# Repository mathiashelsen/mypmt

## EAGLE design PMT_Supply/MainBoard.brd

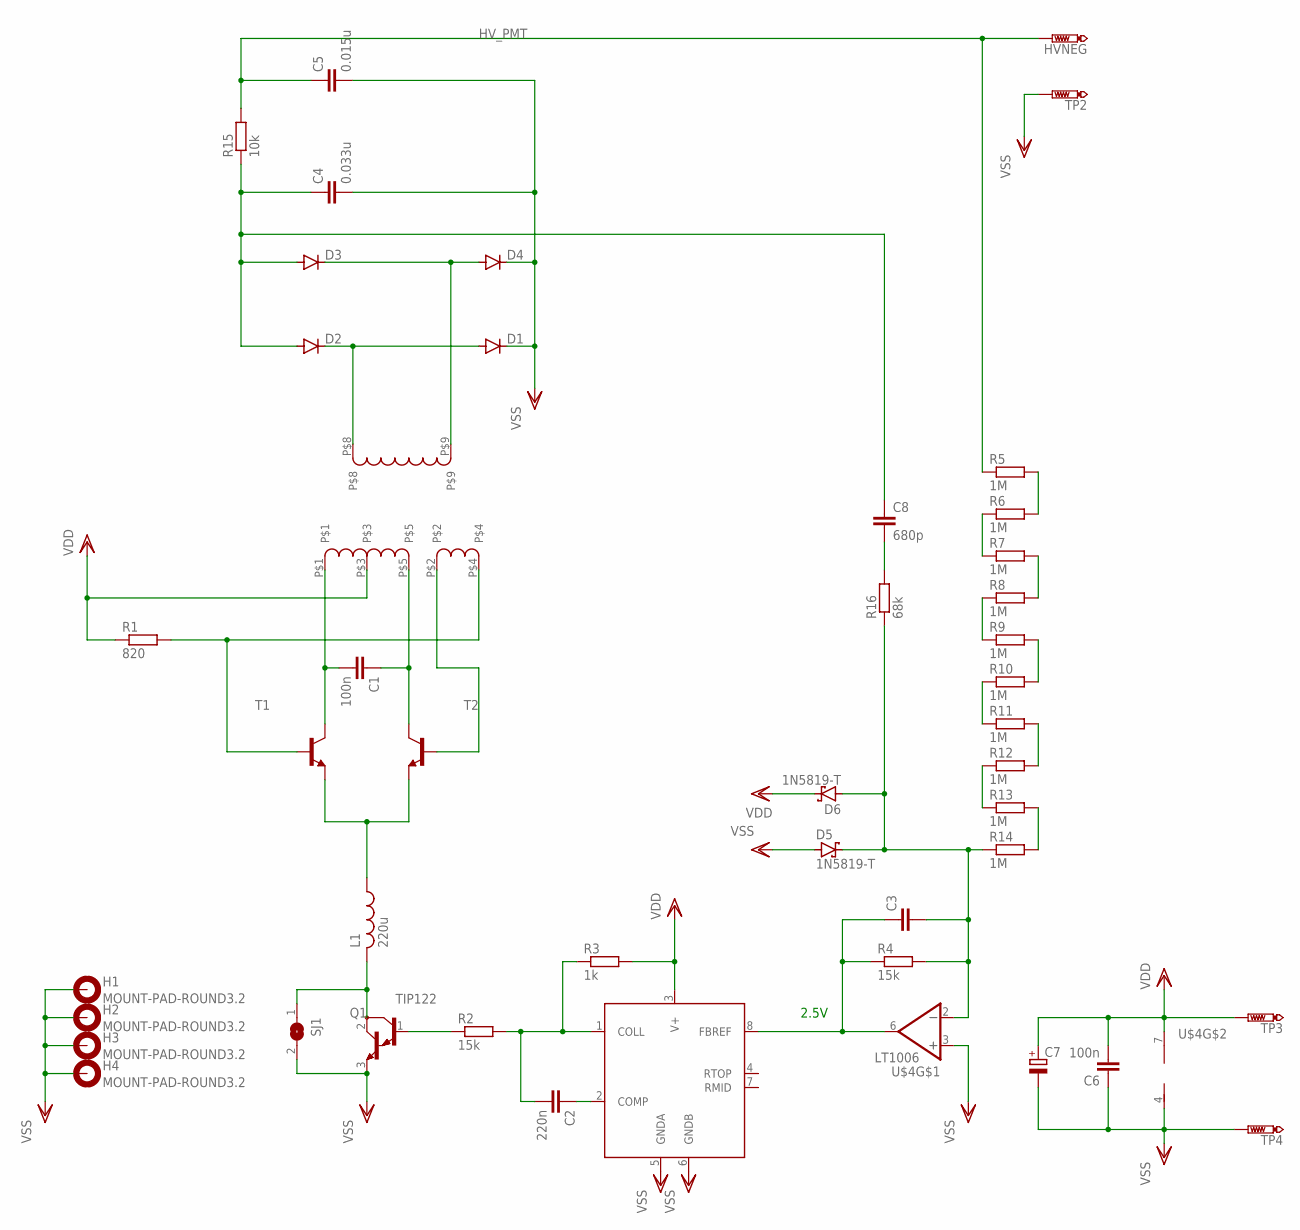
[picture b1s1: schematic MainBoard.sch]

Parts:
C1, C6: 100n; C075-032X103
C2: 220n; C050-035X075
C3: C-EU075-032X103; C075-032X103
C4: 0.033u; C225-087X268
C5: 0.015u; C225-087X268
C7: CPOL-EUE2.5-7; E2,5-7
C8: 680p; C150-064X183
D1, D2, D3, D4: DIODE-DO41-10; DO41-10
D5, D6: 1N5819-T; DO41-7.6
H1, H2, H3, H4: MOUNT-PAD-ROUND3.2; 3,2-PAD
HVNEG: PTR1PAD1-13Y; P1-13Y
L1: 220u; 0207/15
Q1: TIP122; TO220
R1: 820; 0207/7
R2, R4: 15k; 0207/7
R3: 1k; 0207/7
R5, R6, R7, R8, R9, R10, R11, R12, R13, R14: 1M; 0207/7
R15: 10k; 0207/7
R16: 68k; 0207/7
SJ1: SJ
T1, T2: -NPN-TO92-EBC; TO92-EBC
TP2, TP3, TP4: PTR1PAD1-13Y; P1-13Y
U$1: FL2015; FL2015-A
U$3: LT1431; SO08
U$4: LT1006; SO08

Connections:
HV_PMT: C5.1, HVNEG.TP, R5.1, R15.2
unnamed: L1.1, T1.E, T2.E
unnamed: C1.2, T1.C, U$1.P$1
unnamed: C1.1, T2.C, U$1.P$5
unnamed: T2.B, U$1.P$2
unnamed: R1.2, T1.B, U$1.P$4
unnamed: L1.2, Q1.2 (C), SJ1.1
unnamed: D3.C, D4.A, U$1.P$9
unnamed: D1.A, D2.C, U$1.P$8
unnamed: Q1.1 (B), R2.1
unnamed: C2.2, R2.2, R3.1, U$3.1 (COLL)
unnamed: C3.2, D5.C, D6.A, R4.2, R14.1, R16.1, U$4.2 (-IN)
unnamed: C2.1, U$3.2 (COMP)
unnamed: C3.1, R4.1, U$3.8 (FBREF), U$4.6 (OUT)
unnamed: C4.1, C8.1, D2.A, D3.A, R15.1
unnamed: R5.2, R6.2
unnamed: R6.1, R7.1
unnamed: R7.2, R8.2
unnamed: R8.1, R9.1
unnamed: R9.2, R10.2
unnamed: R10.1, R11.1
unnamed: R11.2, R12.2
unnamed: R12.1, R13.1
unnamed: R13.2, R14.2
unnamed: C8.2, R16.2
VDD: C6.2, C7.+, D6.C, R1.1, R3.2, TP3.TP, U$1.P$3, U$3.3 (V+), U$4.7 (V+)
VSS: C4.2, C5.2, C6.1, C7.-, D1.C, D4.C, D5.A, H1.B3,2, H2.B3,2, H3.B3,2, H4.B3,2, Q1.3 (E), SJ1.2, TP2.TP, TP4.TP, U$3.5 (GNDA), U$3.6 (GNDB), U$4.3 (+IN), U$4.4 (V-)

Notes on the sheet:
2.5V

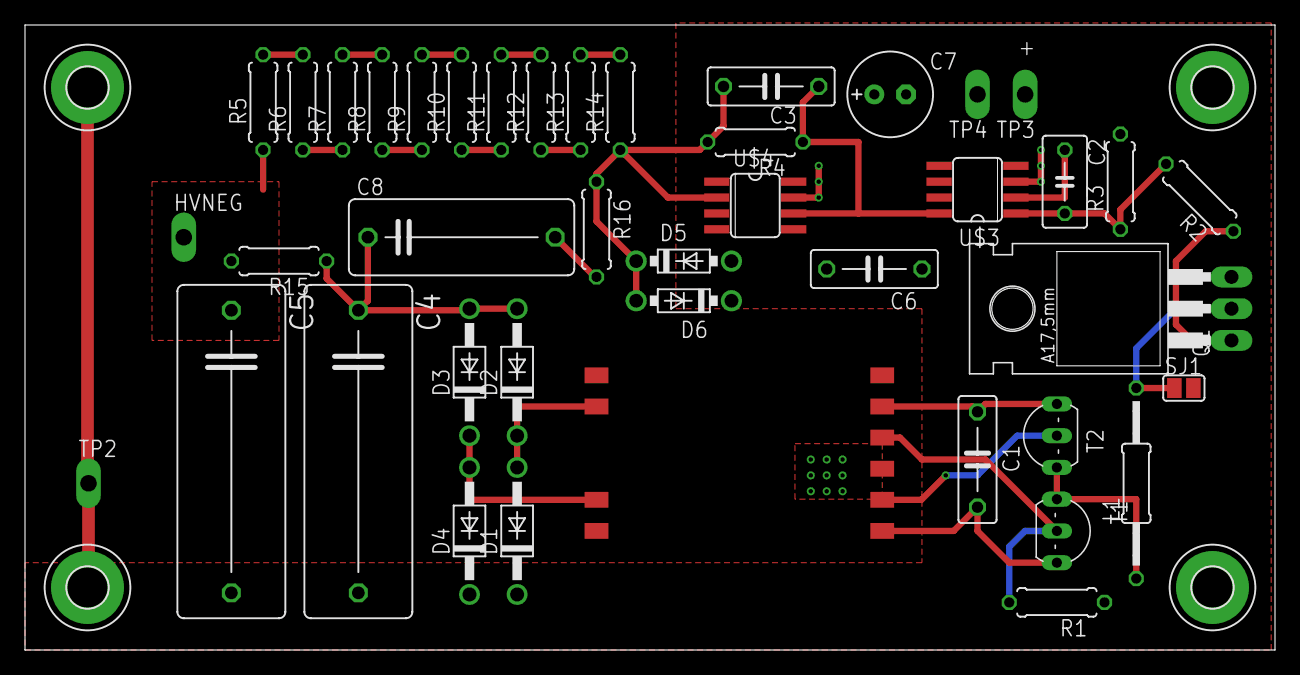
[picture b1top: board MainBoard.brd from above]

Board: 2 copper layers, 100.0 x 50.0 mm, 46 parts (0 on the bottom side), 27 nets.

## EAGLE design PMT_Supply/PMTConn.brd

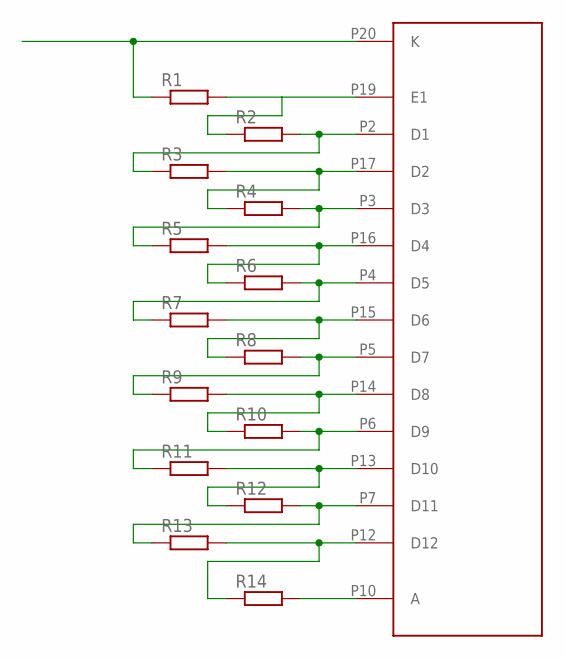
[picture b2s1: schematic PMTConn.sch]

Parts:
R1, R2, R3, R4, R5, R6, R7, R8, R9, R10, R11, R12, R13, R14: R-EU_0207/2V; 0207/2V
U$1: M12FQC51; PMT

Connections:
unnamed: R1.1, U$1.P20 (K)
unnamed: R1.2, R2.1, U$1.P19 (E1)
unnamed: R2.2, R3.1, U$1.P2 (D1)
unnamed: R3.2, R4.1, U$1.P17 (D2)
unnamed: R4.2, R5.1, U$1.P3 (D3)
unnamed: R5.2, R6.1, U$1.P16 (D4)
unnamed: R6.2, R7.1, U$1.P4 (D5)
unnamed: R7.2, R8.1, U$1.P15 (D6)
unnamed: R8.2, R9.1, U$1.P5 (D7)
unnamed: R9.2, R10.1, U$1.P14 (D8)
unnamed: R10.2, R11.1, U$1.P6 (D9)
unnamed: R11.2, R12.1, U$1.P13 (D10)
unnamed: R12.2, R13.1, U$1.P7 (D11)
unnamed: R13.2, R14.1, U$1.P12 (D12)
unnamed: R14.2, U$1.P10 (A)

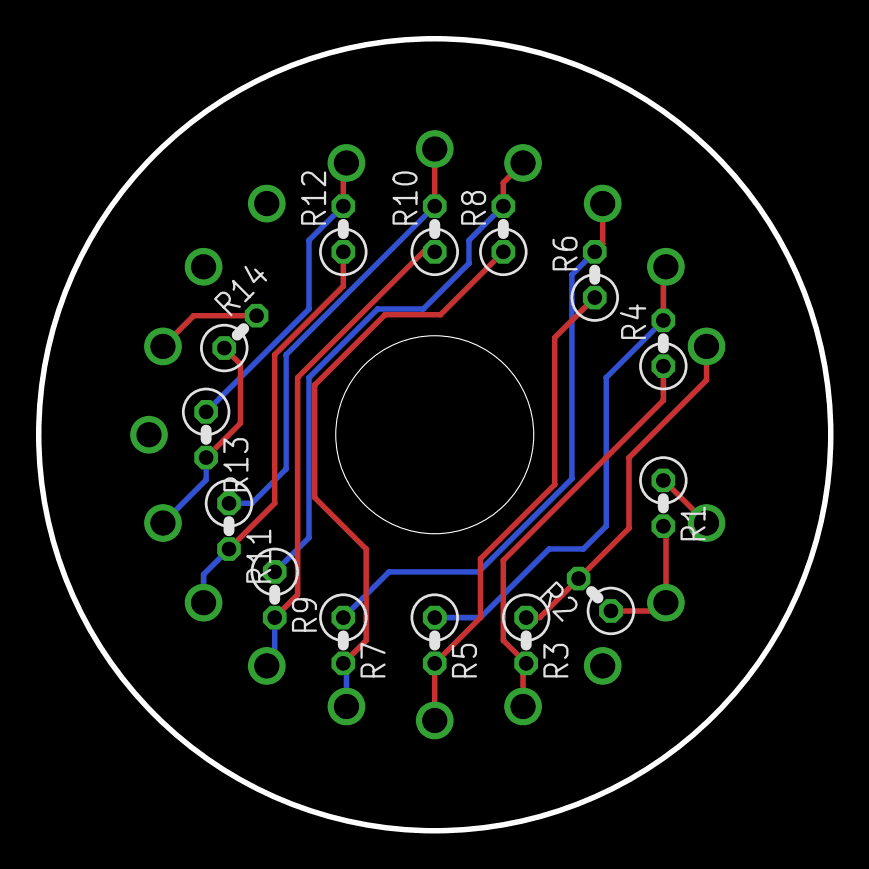
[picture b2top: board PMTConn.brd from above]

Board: 2 copper layers, 44.0 x 44.0 mm, 15 parts (0 on the bottom side), 15 nets.

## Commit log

2023-11-24 Initial commit
    Adding all these files before I possibly lose them
2023-11-30 Adding doc about the PMT
    Adding doc about the PMT
